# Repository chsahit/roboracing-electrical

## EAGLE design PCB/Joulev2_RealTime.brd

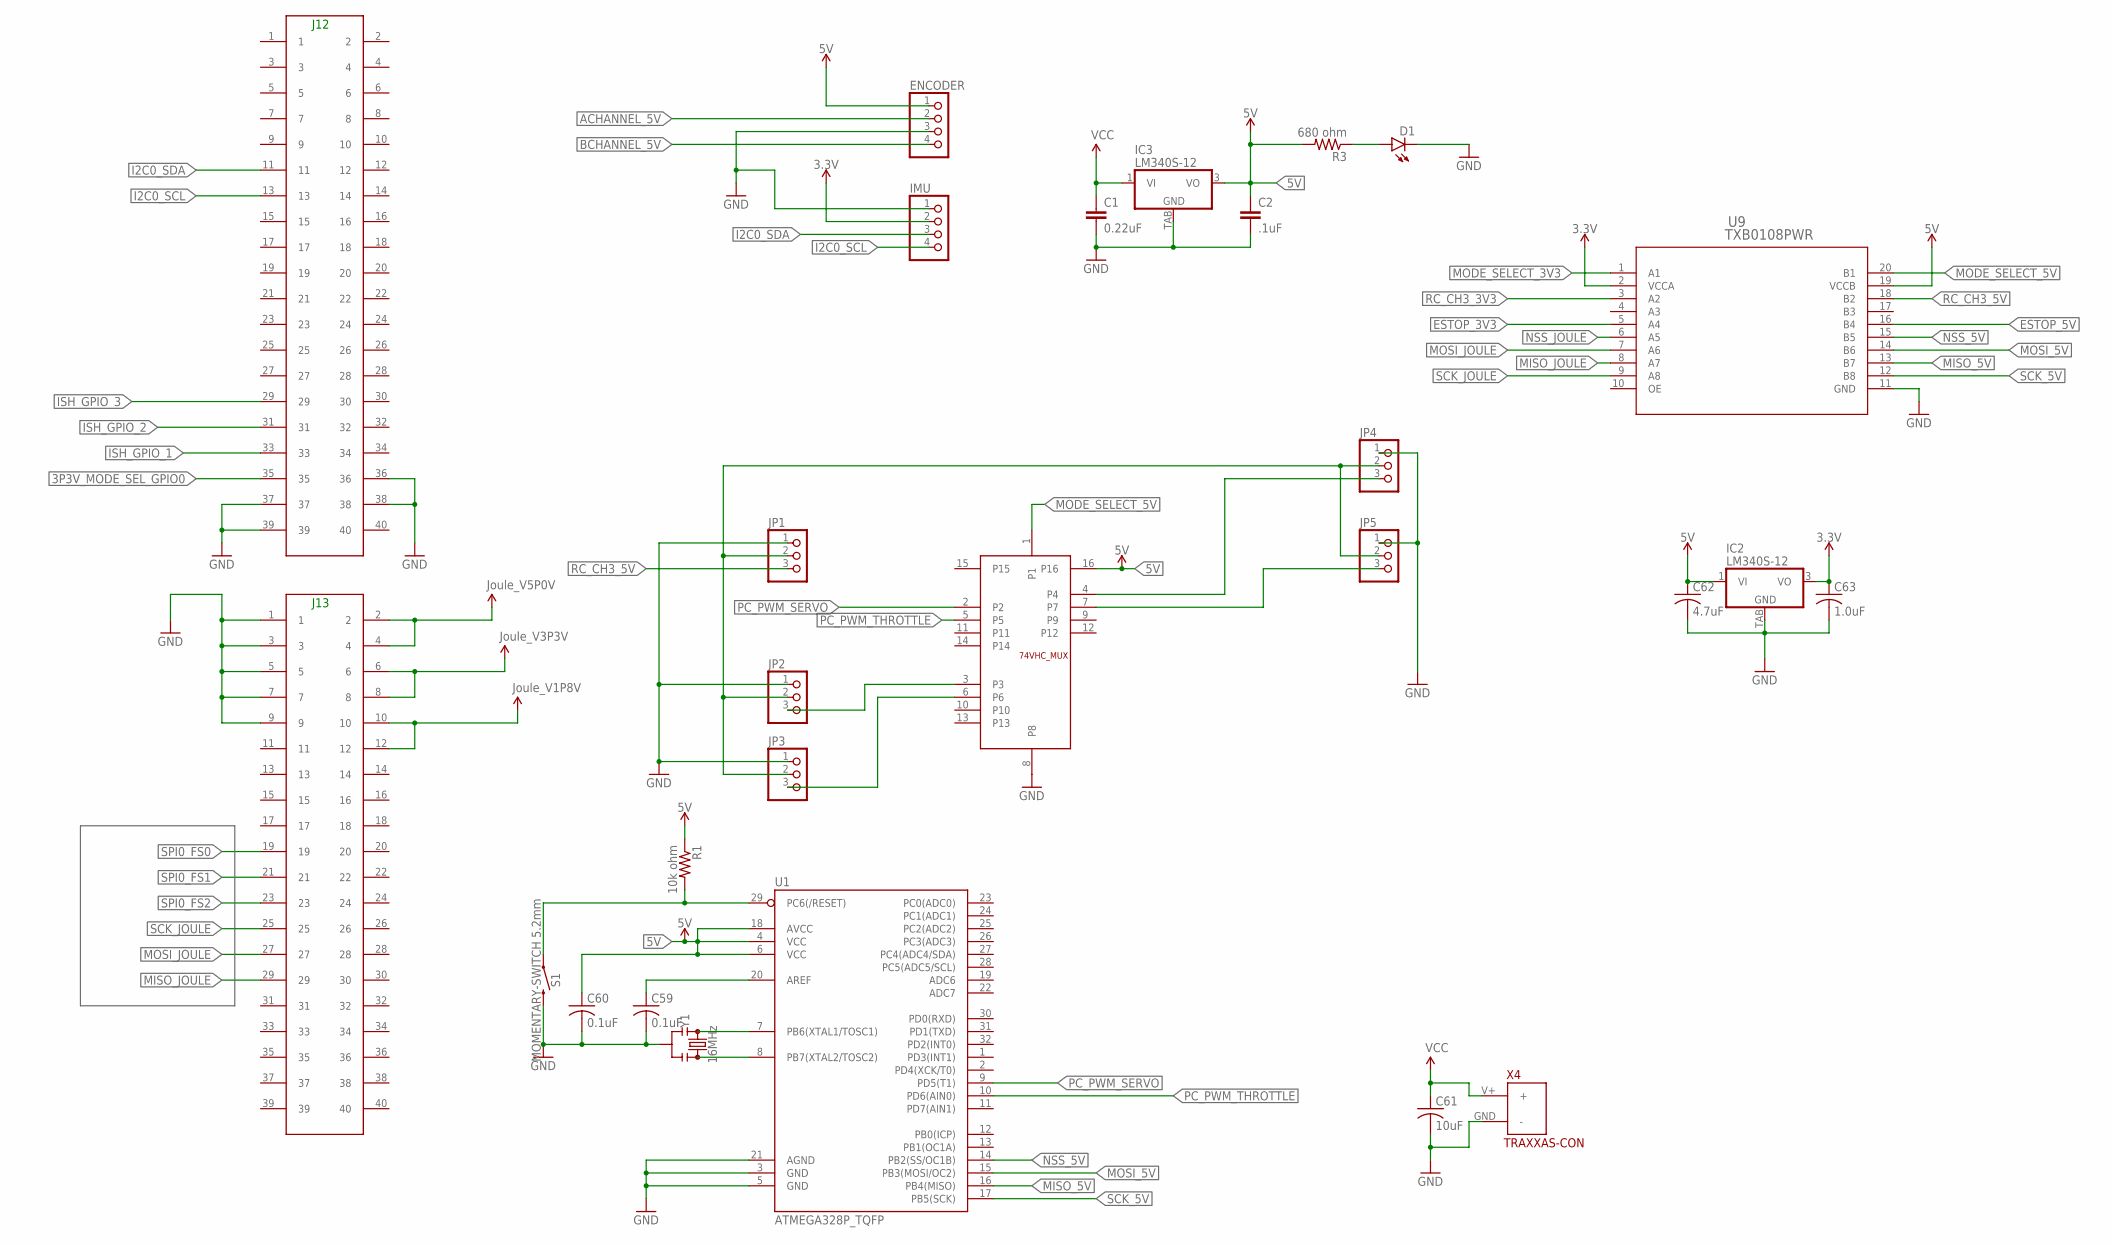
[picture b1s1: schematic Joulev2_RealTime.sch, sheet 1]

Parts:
C1: 0.22uF; 0603-CAP
C2: .1uF; 0603-CAP
C59, C60: 0.1uF; C0603
C61: 10uF; C0603
C62: 4.7uF; C0603
C63: 1.0uF; C0603
D1: LED0603; LED-0603
ENCODER: PINHD-1X4; 1X04
IC2, IC3: LM340S-12; TO263-3
IMU: PINHD-1X4; 1X04
JP1, JP2, JP3, JP4, JP5: PINHD-1X3; 1X03
R1: 10k ohm; R0603
R3: 680 ohm; R0603
S1: MOMENTARY-SWITCH 5.2mm; TACTILE_SWITCH_SMD_5.2MM
U1: ATMEGA328P_TQFP; TQFP32-08
U2: 74VHC_MUXSO16; SO16
U9: TXB0108PWR; PW20
X1: J12HEADER_(JOULE); 2X20
X2: J13HEADER_(JOULE); 2X20
X4: TRAXXAS-CON
Y1: 16MHz; RESONATOR-SMD-3.2X1.3

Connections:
3.3V: C63.1, IC2.3 (VO), IMU.2, U9.2 (VCCA); also elsewhere on the board
3P3V_MODE_SEL_GPIO0: X1.35
5V: C2.1, C60.1, C62.1, ENCODER.1, IC2.1 (VI), IC3.3 (VO), R1.1, R3.2, U1.4 (VCC), U1.6 (VCC), U1.18 (AVCC), U2.16, U9.19 (VCCB)
ACHANNEL_5V: ENCODER.2
BCHANNEL_5V: ENCODER.4
ESTOP_3V3: U9.5 (A4); also elsewhere on the board
ESTOP_5V: U9.16 (B4); also elsewhere on the board
GND: C1.2, C2.2, C59.2, C60.2, C61.2, C62.2, C63.2, D1.C, ENCODER.3, IC2.TAB (GND), IC3.TAB (GND), IMU.1, JP1.1, JP2.1, JP3.1, JP4.1, JP5.1, S1.3 (2), U1.3 (GND), U1.5 (GND), U1.21 (AGND), U2.8, U9.11 (GND), X1.36, X1.37, X1.38, X1.39, X2.1, X2.3, X2.5, X2.7, X2.9, X4.GND (-), Y1.2; also elsewhere on the board
I2C0_SCL: IMU.4, X1.13
I2C0_SDA: IMU.3, X1.11
ISH_GPIO_1: X1.33
ISH_GPIO_2: X1.31
ISH_GPIO_3: X1.29
MISO_5V: U1.16 (PB4(MISO)), U9.13 (B7)
MISO_JOULE: U9.8 (A7), X2.29
MODE_SELECT_3V3: U9.1 (A1); also elsewhere on the board
MODE_SELECT_5V: U2.1, U9.20 (B1)
MOSI_5V: U1.15 (PB3(MOSI/OC2)), U9.14 (B6)
MOSI_JOULE: U9.7 (A6), X2.27
unnamed: JP4.3, U2.4
unnamed: JP5.3, U2.7
unnamed: R1.2, S1.1, U1.29 (PC6(/RESET))
unnamed: U1.7 (PB6(XTAL1/TOSC1)), Y1.1
unnamed: JP1.2, JP2.2, JP3.2, JP4.2, JP5.2
unnamed: U1.8 (PB7(XTAL2/TOSC2)), Y1.3
unnamed: JP2.3, U2.3
unnamed: JP3.3, U2.6
unnamed: C59.1, U1.20 (AREF)
unnamed: D1.A, R3.1
NSS_5V: U1.14 (PB2(SS/OC1B)), U9.15 (B5)
NSS_JOULE: U9.6 (A5)
PC_PWM_SERVO: U1.9 (PD5(T1)), U2.2
PC_PWM_THROTTLE: U1.10 (PD6(AIN0)), U2.5
RC_CH3_3V3: U9.3 (A2); also elsewhere on the board
RC_CH3_5V: JP1.3, U9.18 (B2)
SCK_5V: U1.17 (PB5(SCK)), U9.12 (B8)
SCK_JOULE: U9.9 (A8), X2.25
SPI0_FS0: X2.19
SPI0_FS1: X2.21
SPI0_FS2: X2.23
V1P8V: X2.10, X2.12
V3P3V: X2.6, X2.8
V5P0V: X2.2, X2.4
VCC: C1.1, C61.1, IC3.1 (VI), X4.V+ (+); also elsewhere on the board

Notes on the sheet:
J12
J13

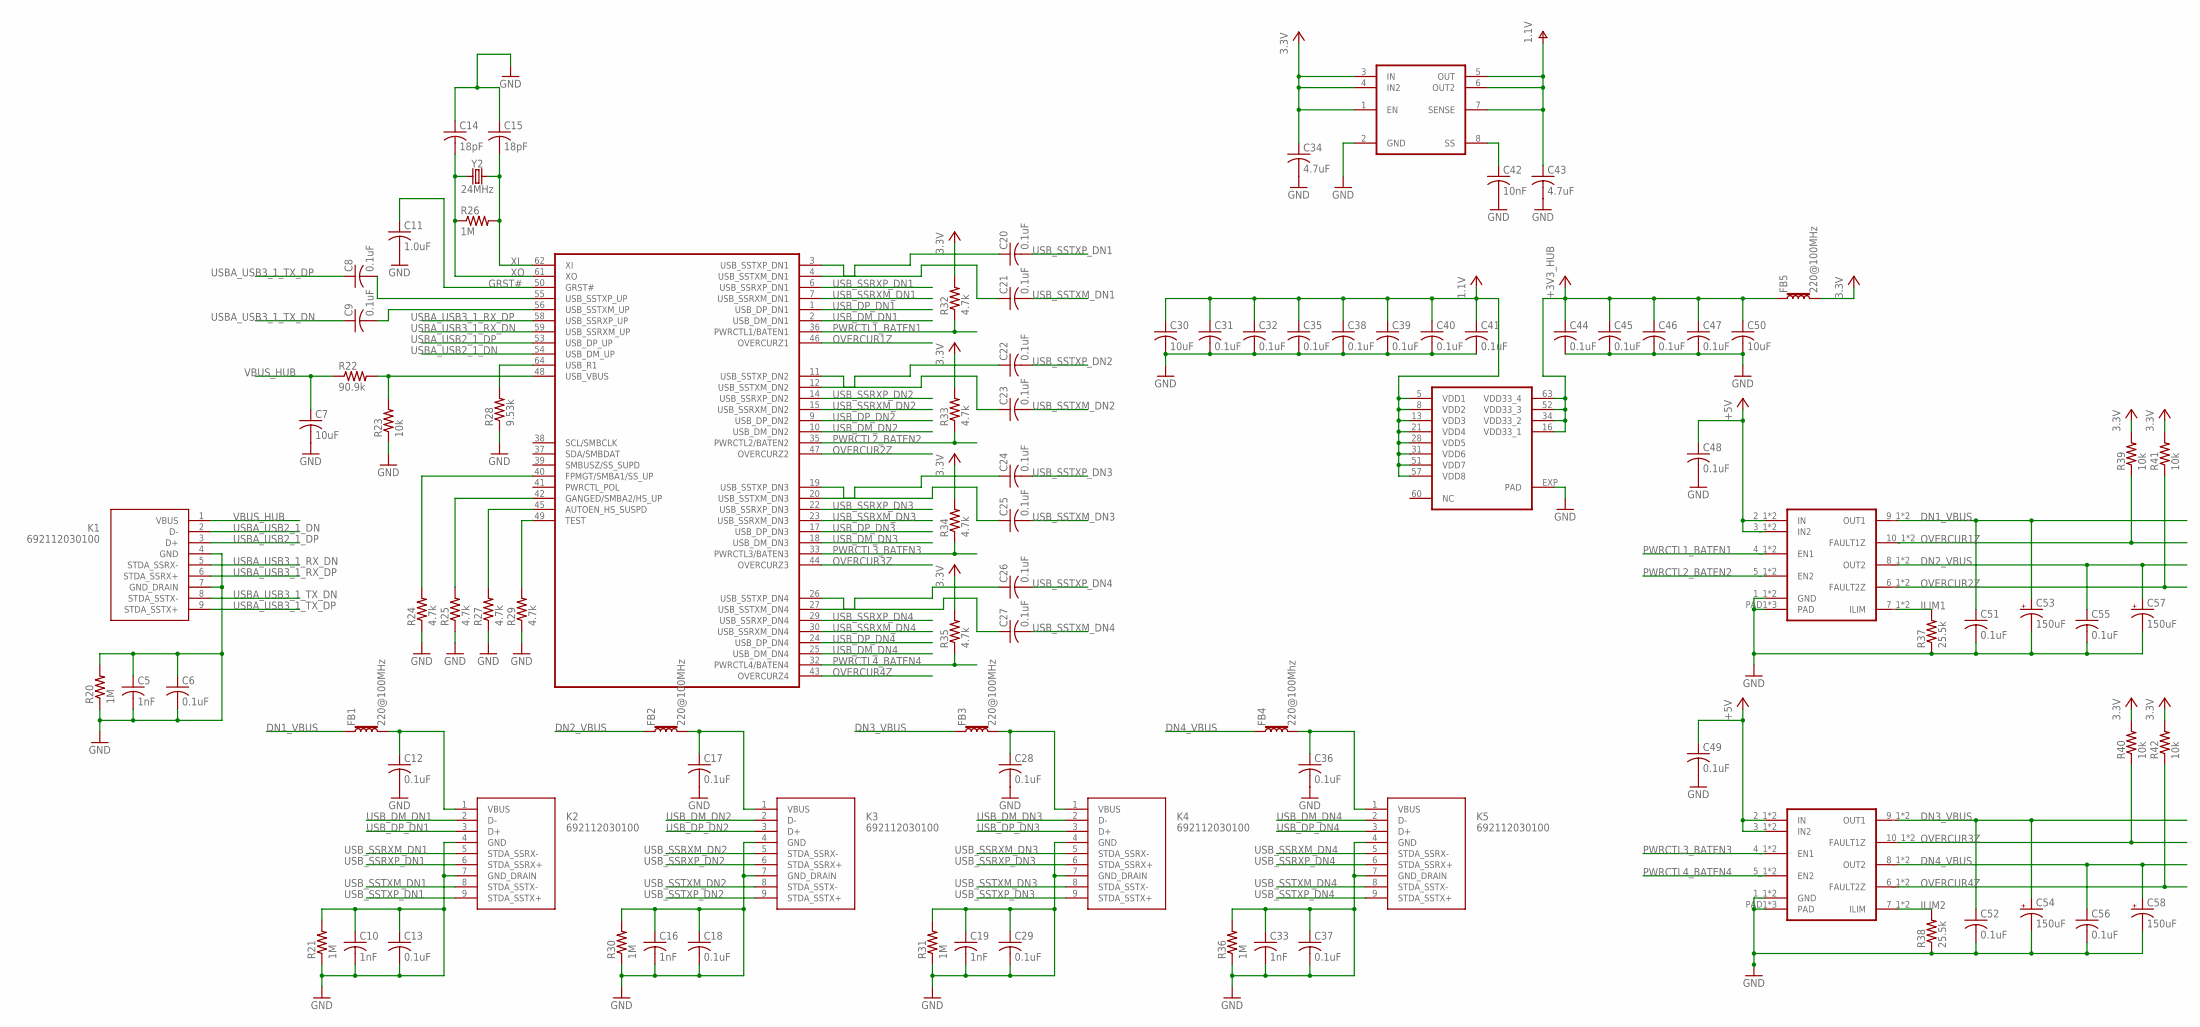
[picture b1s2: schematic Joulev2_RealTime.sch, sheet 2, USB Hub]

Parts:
C5, C10, C16, C19, C33: 1nF; C0603
C6, C12, C13, C17, C18, C28, C29, C31, C32, C35, C36, C37, C38, C39, C40, C41, C44, C45, C46, C47, C48, C49, C51, C52, C55, C56: 0.1uF; C0603
C7, C30, C50: 10uF; C0603
C8, C9, C20, C21, C22, C23, C24, C25, C26, C27: 0.1uF; C0402
C11: 1.0uF; C0603
C14, C15: 18pF; C0603
C34, C43: 4.7uF; C0603
C42: 10nF; C0603
C53, C54, C57, C58: 150uF; CPOL-RADIAL-2.5MM-6.5MM
FB1, FB2, FB3, FB5: 220@100MHz; 0603
FB4: 220@100Mhz; 0603
K1, K2, K3, K4, K5: 692112030100
R20, R21, R26, R30, R31, R36: 1M; R0603
R22: 90.9k; R0603
R23, R39, R40, R41, R42: 10k; R0603
R24, R25, R27, R29, R32, R33, R34, R35: 4.7k; R0603
R28: 9.53k; R0603
R37, R38: 25.5k; R0603
U4: TUSB8041; QFN64-9X9
U5: ADP1706ARDZ-1.1-R7; SOIC8
U6, U7: TPS2561DRCT; 10-VSON
Y2: 24MHz; CRYSTAL-SMD-5X3.2-4PAD

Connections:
1.1V: C30.1, C31.1, C32.1, C35.1, C38.1, C39.1, C40.1, C41.1, C43.1, U4.5 (VDD1), U4.8 (VDD2), U4.13 (VDD3), U4.21 (VDD4), U4.28 (VDD5), U4.31 (VDD6), U4.51 (VDD7), U4.57 (VDD8), U5.5 (OUT), U5.6 (OUT2), U5.7 (SENSE)
3.3V: C34.1, FB5.2, R32.2, R33.2, R34.2, R35.2, R39.2, R40.2, R41.2, R42.2, U5.1 (EN), U5.3 (IN), U5.4 (IN2); also elsewhere on the board
+3V3_HUB: C44.1, C45.1, C46.1, C47.1, C50.1, FB5.1, U4.16 (VDD33_1), U4.34 (VDD33_2), U4.52 (VDD33_3), U4.63 (VDD33_4)
+5V: C48.1, C49.1, U6.2_1 (IN), U6.2_2 (IN), U6.3_1 (IN2), U6.3_2 (IN2), U7.2_1 (IN), U7.2_2 (IN), U7.3_1 (IN2), U7.3_2 (IN2)
DN1_VBUS: C51.1, C53.1 (+), FB1.1, U6.9_1 (OUT1), U6.9_2 (OUT1)
DN2_VBUS: C55.1, C57.1 (+), FB2.1, U6.8_1 (OUT2), U6.8_2 (OUT2)
DN3_VBUS: C52.1, C54.1 (+), FB3.1, U7.9_1 (OUT1), U7.9_2 (OUT1)
DN4_VBUS: C56.1, C58.1 (+), FB4.1, U7.8_1 (OUT2), U7.8_2 (OUT2)
GND: C5.1, C5.2, C6.1, C6.2, C7.2, C10.1, C10.2, C11.2, C12.2, C13.1, C13.2, C14.1, C15.1, C16.1, C16.2, C17.2, C18.1, C18.2, C19.1, C19.2, C28.2, C29.1, C29.2, C30.2, C31.2, C32.2, C33.1, C33.2, C34.2, C35.2, C36.2, C37.1, C37.2, C38.2, C39.2, C40.2, C41.2, C42.2, C43.2, C44.2, C45.2, C46.2, C47.2, C48.2, C49.2, C50.2, C51.2, C52.2, C53.2 (-), C54.2 (-), C55.2, C56.2, C57.2 (-), C58.2 (-), K1.4 (GND), K1.7 (GND_DRAIN), K2.4 (GND), K2.7 (GND_DRAIN), K3.4 (GND), K3.7 (GND_DRAIN), K4.4 (GND), K4.7 (GND_DRAIN), K5.4 (GND), K5.7 (GND_DRAIN), R20.1, R20.2, R21.1, R21.2, R23.1, R24.1, R25.1, R27.1, R28.1, R29.1, R30.1, R30.2, R31.1, R31.2, R36.1, R36.2, R37.1, R38.1, U4.EXP (PAD), U5.2 (GND), U6.1_1 (GND), U6.1_2 (GND), U6.PAD1 (PAD), U6.PAD2 (PAD), U6.PAD3 (PAD), U7.1_1 (GND), U7.1_2 (GND), U7.PAD1 (PAD), U7.PAD2 (PAD), U7.PAD3 (PAD); also elsewhere on the board
GRST#: C11.1, U4.50 (GRST#)
ILIM1: R37.2, U6.7_1 (ILIM), U6.7_2 (ILIM)
ILIM2: R38.2, U7.7_1 (ILIM), U7.7_2 (ILIM)
unnamed: R28.2, U4.64 (USB_R1)
unnamed: R29.2, U4.49 (TEST)
unnamed: R27.2, U4.45 (AUTOEN_HS_SUSPD)
unnamed: R25.2, U4.42 (GANGED/SMBA2/HS_UP)
unnamed: R24.2, U4.40 (FPMGT/SMBA1/SS_UP)
unnamed: R22.2, R23.2, U4.48 (USB_VBUS)
unnamed: C27.1, U4.26 (USB_SSTXP_DN4)
unnamed: C26.1, U4.27 (USB_SSTXM_DN4)
unnamed: C25.1, U4.19 (USB_SSTXP_DN3)
unnamed: C24.1, U4.20 (USB_SSTXM_DN3)
unnamed: C23.1, U4.11 (USB_SSTXP_DN2)
unnamed: C22.1, U4.12 (USB_SSTXM_DN2)
unnamed: C21.1, U4.3 (USB_SSTXP_DN1)
unnamed: C20.1, U4.4 (USB_SSTXM_DN1)
unnamed: C12.1, FB1.2, K2.1 (VBUS)
unnamed: C42.1, U5.8 (SS)
unnamed: C17.1, FB2.2, K3.1 (VBUS)
unnamed: C28.1, FB3.2, K4.1 (VBUS)
unnamed: C36.1, FB4.2, K5.1 (VBUS)
OVERCUR1Z: R39.1, U4.46 (OVERCURZ1), U6.10_1 (FAULT1Z), U6.10_2 (FAULT1Z)
OVERCUR2Z: R41.1, U4.47 (OVERCURZ2), U6.6_1 (FAULT2Z), U6.6_2 (FAULT2Z)
OVERCUR3Z: R40.1, U4.44 (OVERCURZ3), U7.10_1 (FAULT1Z), U7.10_2 (FAULT1Z)
OVERCUR4Z: R42.1, U4.43 (OVERCURZ4), U7.6_1 (FAULT2Z), U7.6_2 (FAULT2Z)
PWRCTL1_BATEN1: R32.1, U4.36 (PWRCTL1/BATEN1), U6.4_1 (EN1), U6.4_2 (EN1)
PWRCTL2_BATEN2: R33.1, U4.35 (PWRCTL2/BATEN2), U6.5_1 (EN2), U6.5_2 (EN2)
PWRCTL3_BATEN3: R34.1, U4.33 (PWRCTL3/BATEN3), U7.4_1 (EN1), U7.4_2 (EN1)
PWRCTL4_BATEN4: R35.1, U4.32 (PWRCTL4/BATEN4), U7.5_1 (EN2), U7.5_2 (EN2)
USBA_USB2_1_DN: K1.2 (D-), U4.54 (USB_DM_UP)
USBA_USB2_1_DP: K1.3 (D+), U4.53 (USB_DP_UP)
USBA_USB3_1_RX_DN: K1.5 (STDA_SSRX-), U4.59 (USB_SSRXM_UP)
USBA_USB3_1_RX_DP: K1.6 (STDA_SSRX+), U4.58 (USB_SSRXP_UP)
USBA_USB3_1_TX_DN: C9.1, K1.8 (STDA_SSTX-)
USBA_USB3_1_TX_DP: C8.1, K1.9 (STDA_SSTX+)
USB_DM_DN1: K2.2 (D-), U4.2 (USB_DM_DN1)
USB_DM_DN2: K3.2 (D-), U4.10 (USB_DM_DN2)
USB_DM_DN3: K4.2 (D-), U4.18 (USB_DM_DN3)
USB_DM_DN4: K5.2 (D-), U4.25 (USB_DM_DN4)
USB_DP_DN1: K2.3 (D+), U4.1 (USB_DP_DN1)
USB_DP_DN2: K3.3 (D+), U4.9 (USB_DP_DN2)
USB_DP_DN3: K4.3 (D+), U4.17 (USB_DP_DN3)
USB_DP_DN4: K5.3 (D+), U4.24 (USB_DP_DN4)
USB_SSRXM_DN1: K2.5 (STDA_SSRX-), U4.7 (USB_SSRXM_DN1)
USB_SSRXM_DN2: K3.5 (STDA_SSRX-), U4.15 (USB_SSRXM_DN2)
USB_SSRXM_DN3: K4.5 (STDA_SSRX-), U4.23 (USB_SSRXM_DN3)
USB_SSRXM_DN4: K5.5 (STDA_SSRX-), U4.30 (USB_SSRXM_DN4)
USB_SSRXP_DN1: K2.6 (STDA_SSRX+), U4.6 (USB_SSRXP_DN1)
USB_SSRXP_DN2: K3.6 (STDA_SSRX+), U4.14 (USB_SSRXP_DN2)
USB_SSRXP_DN3: K4.6 (STDA_SSRX+), U4.22 (USB_SSRXP_DN3)
USB_SSRXP_DN4: K5.6 (STDA_SSRX+), U4.29 (USB_SSRXP_DN4)
USB_SSTXM_DN1: C21.2, K2.8 (STDA_SSTX-)
USB_SSTXM_DN2: C23.2, K3.8 (STDA_SSTX-)
USB_SSTXM_DN3: C25.2, K4.8 (STDA_SSTX-)
USB_SSTXM_DN4: C27.2, K5.8 (STDA_SSTX-)
USB_SSTXP_DN1: C20.2, K2.9 (STDA_SSTX+)
USB_SSTXP_DN2: C22.2, K3.9 (STDA_SSTX+)
USB_SSTXP_DN3: C24.2, K4.9 (STDA_SSTX+)
USB_SSTXP_DN4: C26.2, K5.9 (STDA_SSTX+)
VBUS_HUB: C7.1, K1.1 (VBUS), R22.1
X: C8.2, U4.55 (USB_SSTXP_UP)
XI: C15.2, R26.2, U4.62 (XI), Y2.3 (2)
XO: C14.2, R26.1, U4.61 (XO), Y2.1
Y: C9.2, U4.56 (USB_SSTXM_UP)

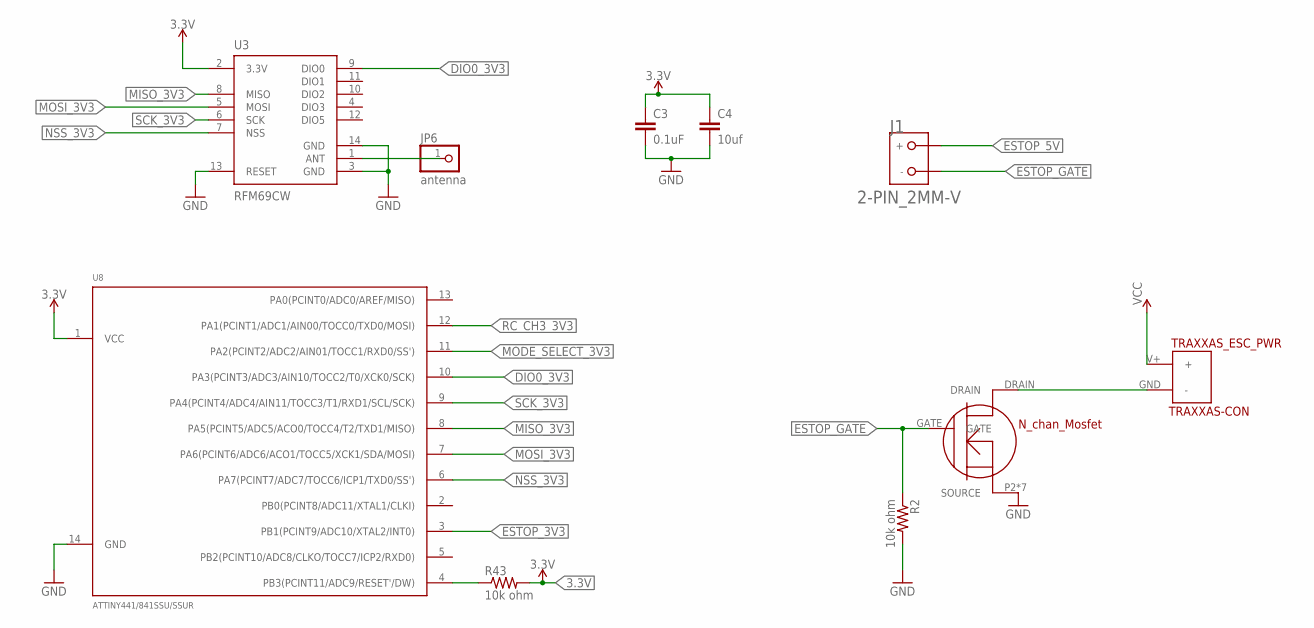
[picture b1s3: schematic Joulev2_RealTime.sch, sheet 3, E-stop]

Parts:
C3: 0.1uF; 0603-CAP
C4: 10uf; 0805@1
J1: 2-PIN_2MM-V; 2MM-2-V
JP6: antenna; 1X01
Q1: N_CH_MOSFET_FDLBL260N100; MO-299A
R2, R43: 10k ohm; R0603
TRAXXAS_ESC_PWR: TRAXXAS-CON
U3: RFM69CW; RFM69CW-XXXS2
U8: ATTINY441/841SSU/SSUR; SOIC-14

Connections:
3.3V: C3.1, C4.1, R43.2, U3.2 (3.3V), U8.1 (VCC); also elsewhere on the board
DIO0_3V3: U3.9 (DIO0), U8.10 (PA3(PCINT3/ADC3/AIN10/TOCC2/T0/XCK0/SCK))
ESTOP_3V3: U8.3 (PB1(PCINT9/ADC10/XTAL2/INT0)); also elsewhere on the board
ESTOP_5V: J1.1 (+); also elsewhere on the board
ESTOP_GATE: J1.2 (-), Q1.GATE, R2.1
GND: C3.2, C4.2, Q1.P2 (SOURCE), Q1.P3 (SOURCE), Q1.P4 (SOURCE), Q1.P5 (SOURCE), Q1.P6 (SOURCE), Q1.P7 (SOURCE), Q1.P8 (SOURCE), R2.2, U3.3 (GND), U3.13 (RESET), U3.14 (GND), U8.14 (GND); also elsewhere on the board
MISO_3V3: U3.8 (MISO), U8.8 (PA5(PCINT5/ADC5/ACO0/TOCC4/T2/TXD1/MISO))
MODE_SELECT_3V3: U8.11 (PA2(PCINT2/ADC2/AIN01/TOCC1/RXD0/SS')); also elsewhere on the board
MOSI_3V3: U3.5 (MOSI), U8.7 (PA6(PCINT6/ADC6/ACO1/TOCC5/XCK1/SDA/MOS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)
unnamed: JP6.1, U3.1 (ANT)
unnamed: R43.1, U8.4 (PB3(PCINT11/ADC9/RESET'/DW))
NSS_3V3: U3.7 (NSS), U8.6 (PA7(PCINT7/ADC7/TOCC6/ICP1/TXD0/SS'))
RC_CH3_3V3: U8.12 (PA1(PCINT1/ADC1/AIN00/TOCC0/TXD0/MOSI)); also elsewhere on the board
SCK_3V3: U3.6 (SCK), U8.9 (PA4(PCINT4/ADC4/AIN11/TOCC3/T1/RXD1/SCL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)
VCC: TRAXXAS_ESC_PWR.V+ (+); also elsewhere on the board

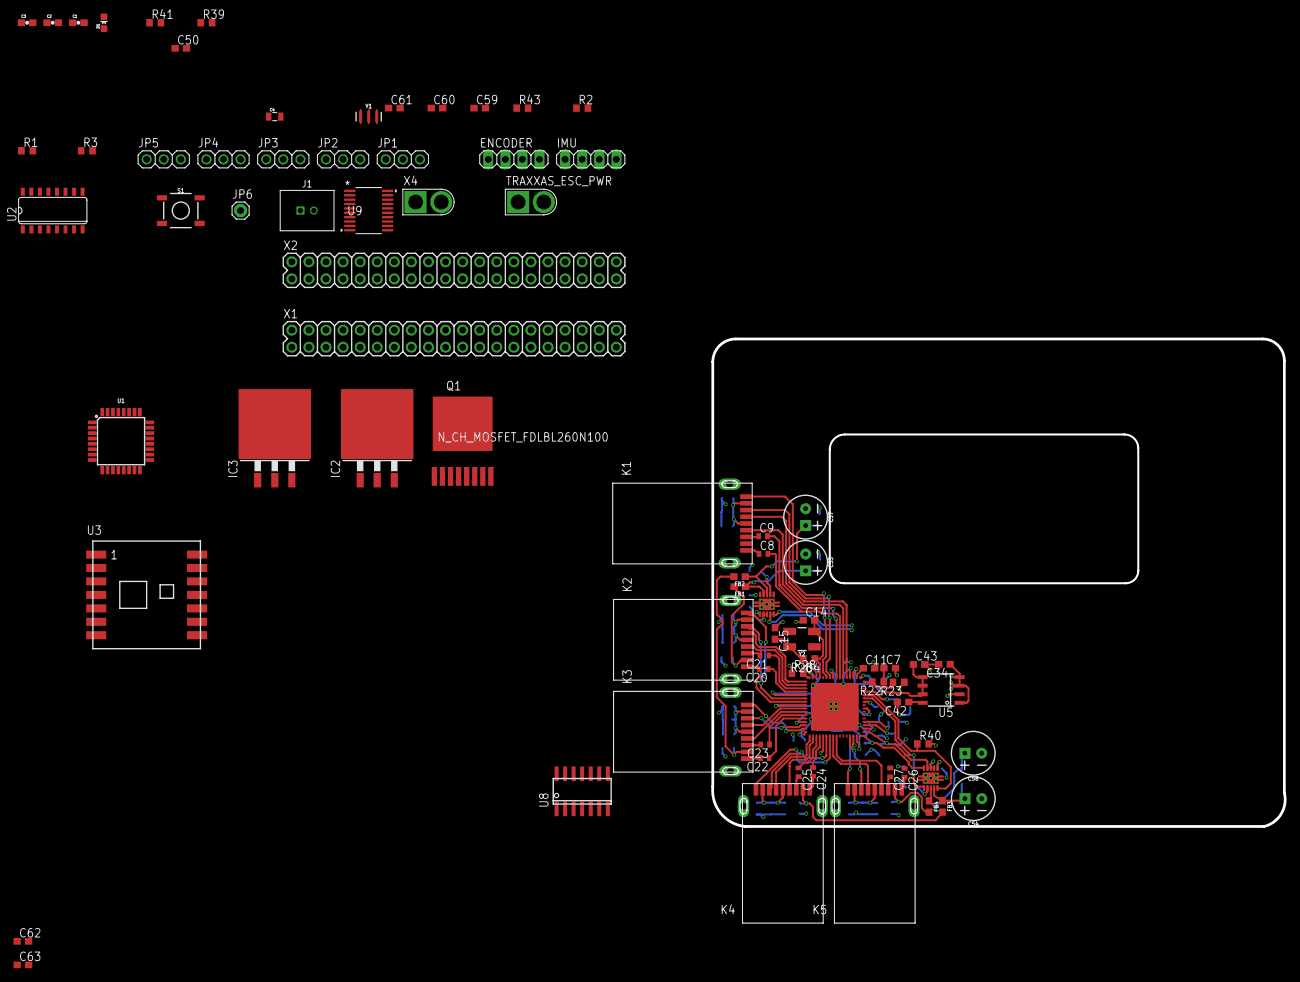
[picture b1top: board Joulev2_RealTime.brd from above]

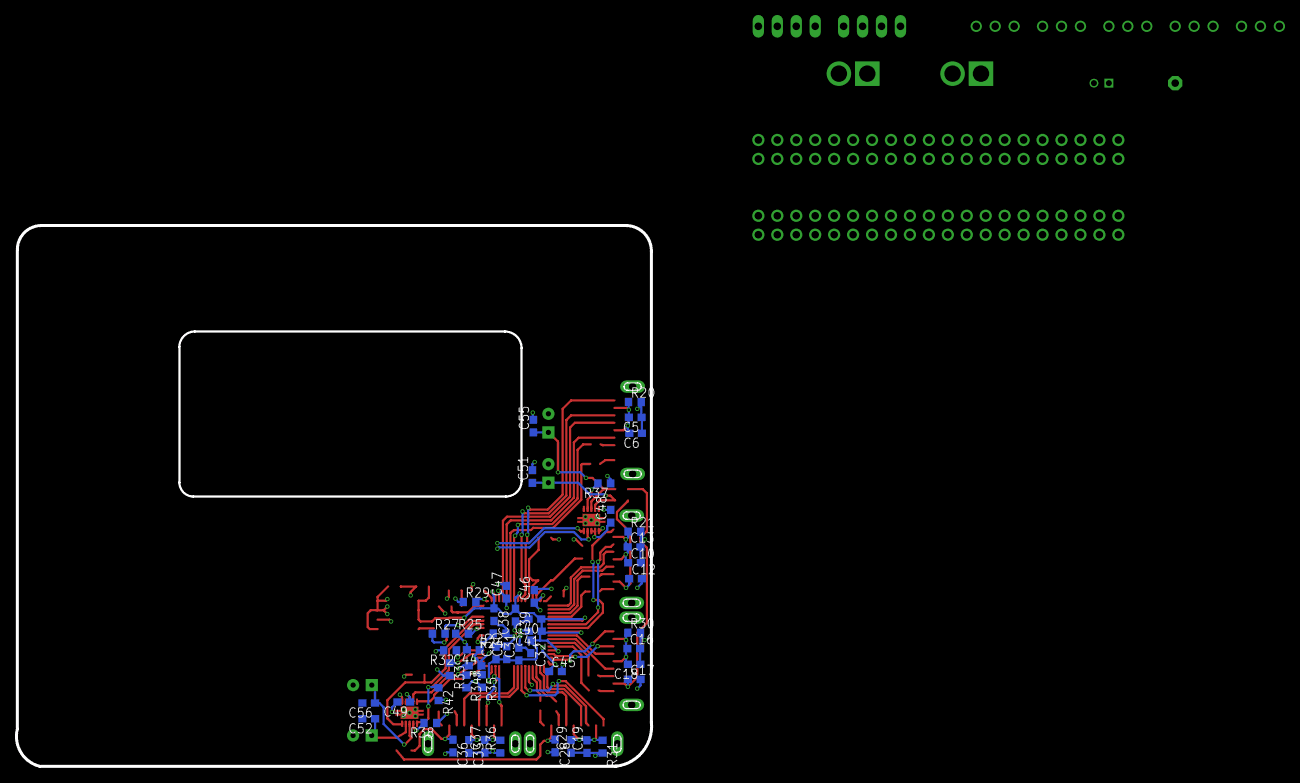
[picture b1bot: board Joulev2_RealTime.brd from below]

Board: 4 copper layers, 85.2 x 72.5 mm, 129 parts (49 on the bottom side), 114 nets.

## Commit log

2017-04-18 Updated minor changes on old board. will now be using shield design.
2017-05-01 inital commit
2017-05-01 05/01/2017
2017-05-05 cinco de mayo
2017-05-06 Revert "Merge remote-tracking branch 'origin/USB2.0' into Joule-Breakout"
    This reverts commit 212b18db0099d8b30c1e8da574bdc43e8d282a24, reversing
    changes made to 2839ac94d3ec3073ea43a796fe64a609bf76dc33.
2017-05-06 Revert "Merge remote-tracking branch 'origin/USB2.0' into Joule-Breakout"
    This reverts commit 2839ac94d3ec3073ea43a796fe64a609bf76dc33, reversing
    changes made to d49a66ea7caaff2f058e7b4f2c8019333170ecc5.

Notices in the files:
parts and their libraries:
SparkFun-Capacitors: Licensing: Creative Commons ShareAlike 4.0 International - https://creativecommons.org/licenses/by-sa/4.0
